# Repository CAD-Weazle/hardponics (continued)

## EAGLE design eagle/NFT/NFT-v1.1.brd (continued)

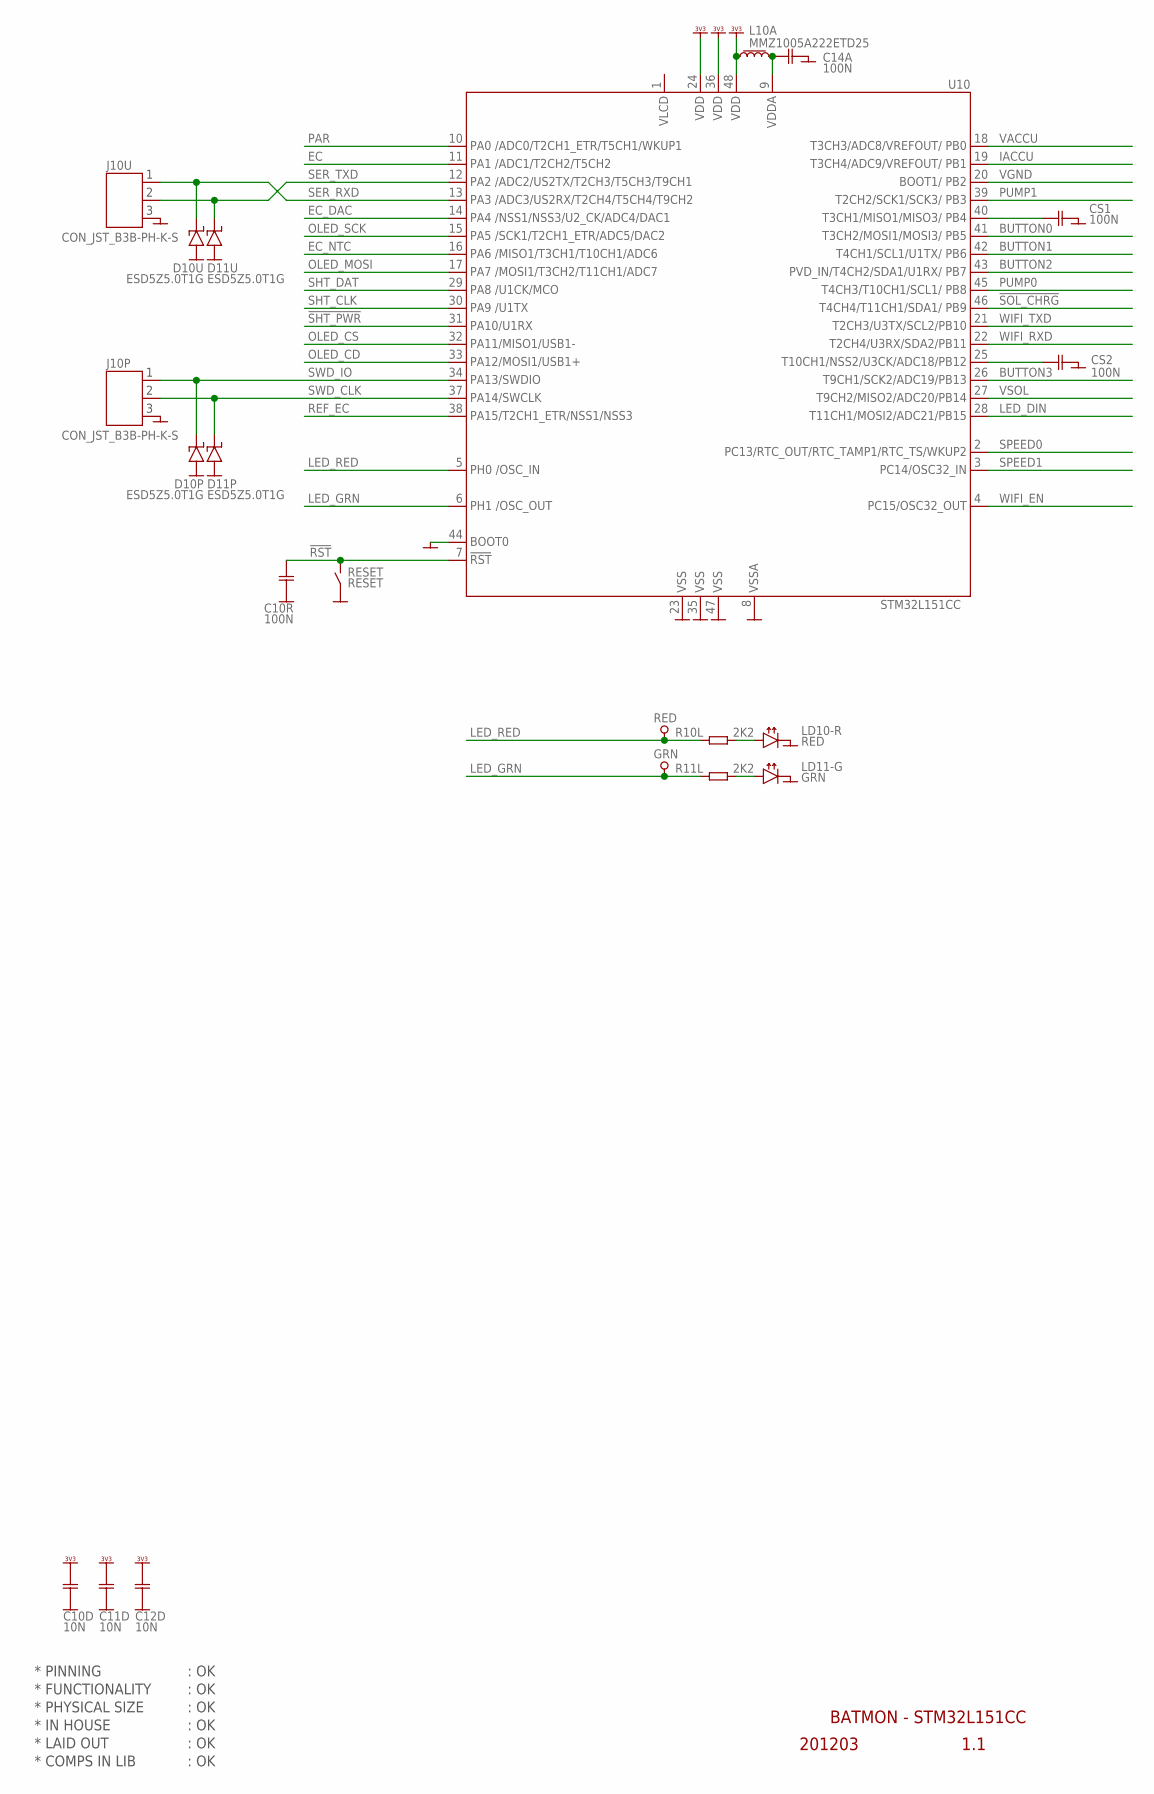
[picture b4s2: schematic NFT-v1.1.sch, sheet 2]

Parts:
C10D, C11D, C12D: 10N; CAP0402
C10R, C14A: 100N; CAP0402
CS1, CS2: 100N; CAP0402
D10P, D10U, D11P, D11U: ESD5Z5.0T1G; DIODE_SOD523
GRN: PIN_TEST_0.6MM; HOLE_PTH_0.6MM
J10P, J10U: CON_JST_B3B-PH-K-S
L10A: MMZ1005A222ETD25; L_0402
LD10-R: RED; LED_SMD_0402
LD11-G: GRN; LED_SMD_0402
R10L, R11L: 2K2; RES0402
RED: PIN_TEST_0.6MM; HOLE_PTH_0.6MM
RESET: RESET; SWITCH_SMD_PBUTTON_2P
U10: STM32L151CC; LQFP48

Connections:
!RST: C10R.1, RESET.1 (1-2), U10.7 (7.!RST)
!SHT_PWR: U10.31 (31.PA10); also elsewhere on the board
!SOL_CHRG: U10.46 (46.PB9); also elsewhere on the board
BUTTON0: U10.41 (41.PB5); also elsewhere on the board
BUTTON1: U10.42 (42.PB6); also elsewhere on the board
BUTTON2: U10.43 (43.PB7); also elsewhere on the board
BUTTON3: U10.26 (26.PB13); also elsewhere on the board
CSAMPLE: CS1.1, U10.40 (40.PB4)
CSAMPLE1: CS2.1, U10.25 (25.PB12)
EC: U10.11 (11.PA1); also elsewhere on the board
EC_DAC: U10.14 (14.PA4); also elsewhere on the board
EC_NTC: U10.16 (16.PA6); also elsewhere on the board
GND: C10D.2, C10R.2, C11D.2, C12D.2, C14A.2, CS1.2, CS2.2, D10P.A, D10U.A, D11P.A, D11U.A, J10P.3, J10U.3, LD10-R.C, LD11-G.C, RESET.2 (3-4), U10.8 (8.GND), U10.23 (23.GND), U10.35 (35.GND), U10.44 (44.BOOT0), U10.47 (47.GND); also elsewhere on the board
IACCU: U10.19 (19.PB1); also elsewhere on the board
LED_DIN: U10.28 (28.PB15); also elsewhere on the board
LED_GRN: GRN.1, R11L.1, U10.6 (6.OSC_OUT)
LED_RED: R10L.1, RED.1, U10.5 (5.OSC_IN)
unnamed: LD11-G.A, R11L.2
unnamed: LD10-R.A, R10L.2
OLED_CD: U10.33 (33.PA12); also elsewhere on the board
OLED_CS: U10.32 (32.PA11); also elsewhere on the board
OLED_MOSI: U10.17 (17.PA7); also elsewhere on the board
OLED_SCK: U10.15 (15.PA5); also elsewhere on the board
PAR: U10.10 (10.PA0); also elsewhere on the board
PUMP0: U10.45 (45.PB8); also elsewhere on the board
PUMP1: U10.39 (39.PB3); also elsewhere on the board
REF_EC: U10.38 (38.PA15); also elsewhere on the board
SER_RXD: D10U.C, J10U.1, U10.13 (13.PA3)
SER_TXD: D11U.C, J10U.2, U10.12 (12.PA2)
SHT_CLK: U10.30 (30.PA9); also elsewhere on the board
SHT_DAT: U10.29 (29.PA8); also elsewhere on the board
SPEED0: U10.2 (2.PC13); also elsewhere on the board
SPEED1: U10.3 (3.PC14); also elsewhere on the board
SWD_CLK: D11P.C, J10P.2, U10.37 (37.PA14)
SWD_IO: D10P.C, J10P.1, U10.34 (34.PA13)
VACCU: U10.18 (18.PB0); also elsewhere on the board
VDDA: C14A.1, L10A.2, U10.9 (9.VDD)
VDD_3V3: C10D.1, C11D.1, C12D.1, L10A.1, U10.24 (24.VDD), U10.36 (36.VDD), U10.48 (48.VDD); also elsewhere on the board
VGND: U10.20 (20.PB2); also elsewhere on the board
VSOL: U10.27 (27.PB14); also elsewhere on the board
WIFI_EN: U10.4 (4.PC15); also elsewhere on the board
WIFI_RXD: U10.22 (22.PB11); also elsewhere on the board
WIFI_TXD: U10.21 (21.PB10); also elsewhere on the board

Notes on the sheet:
* PINNING
* FUNCTIONALITY
* PHYSICAL SIZE
* LAID OUT
* COMPS IN LIB
* IN HOUSE
: OK
BATMON - STM32L151CC
201203
1.1

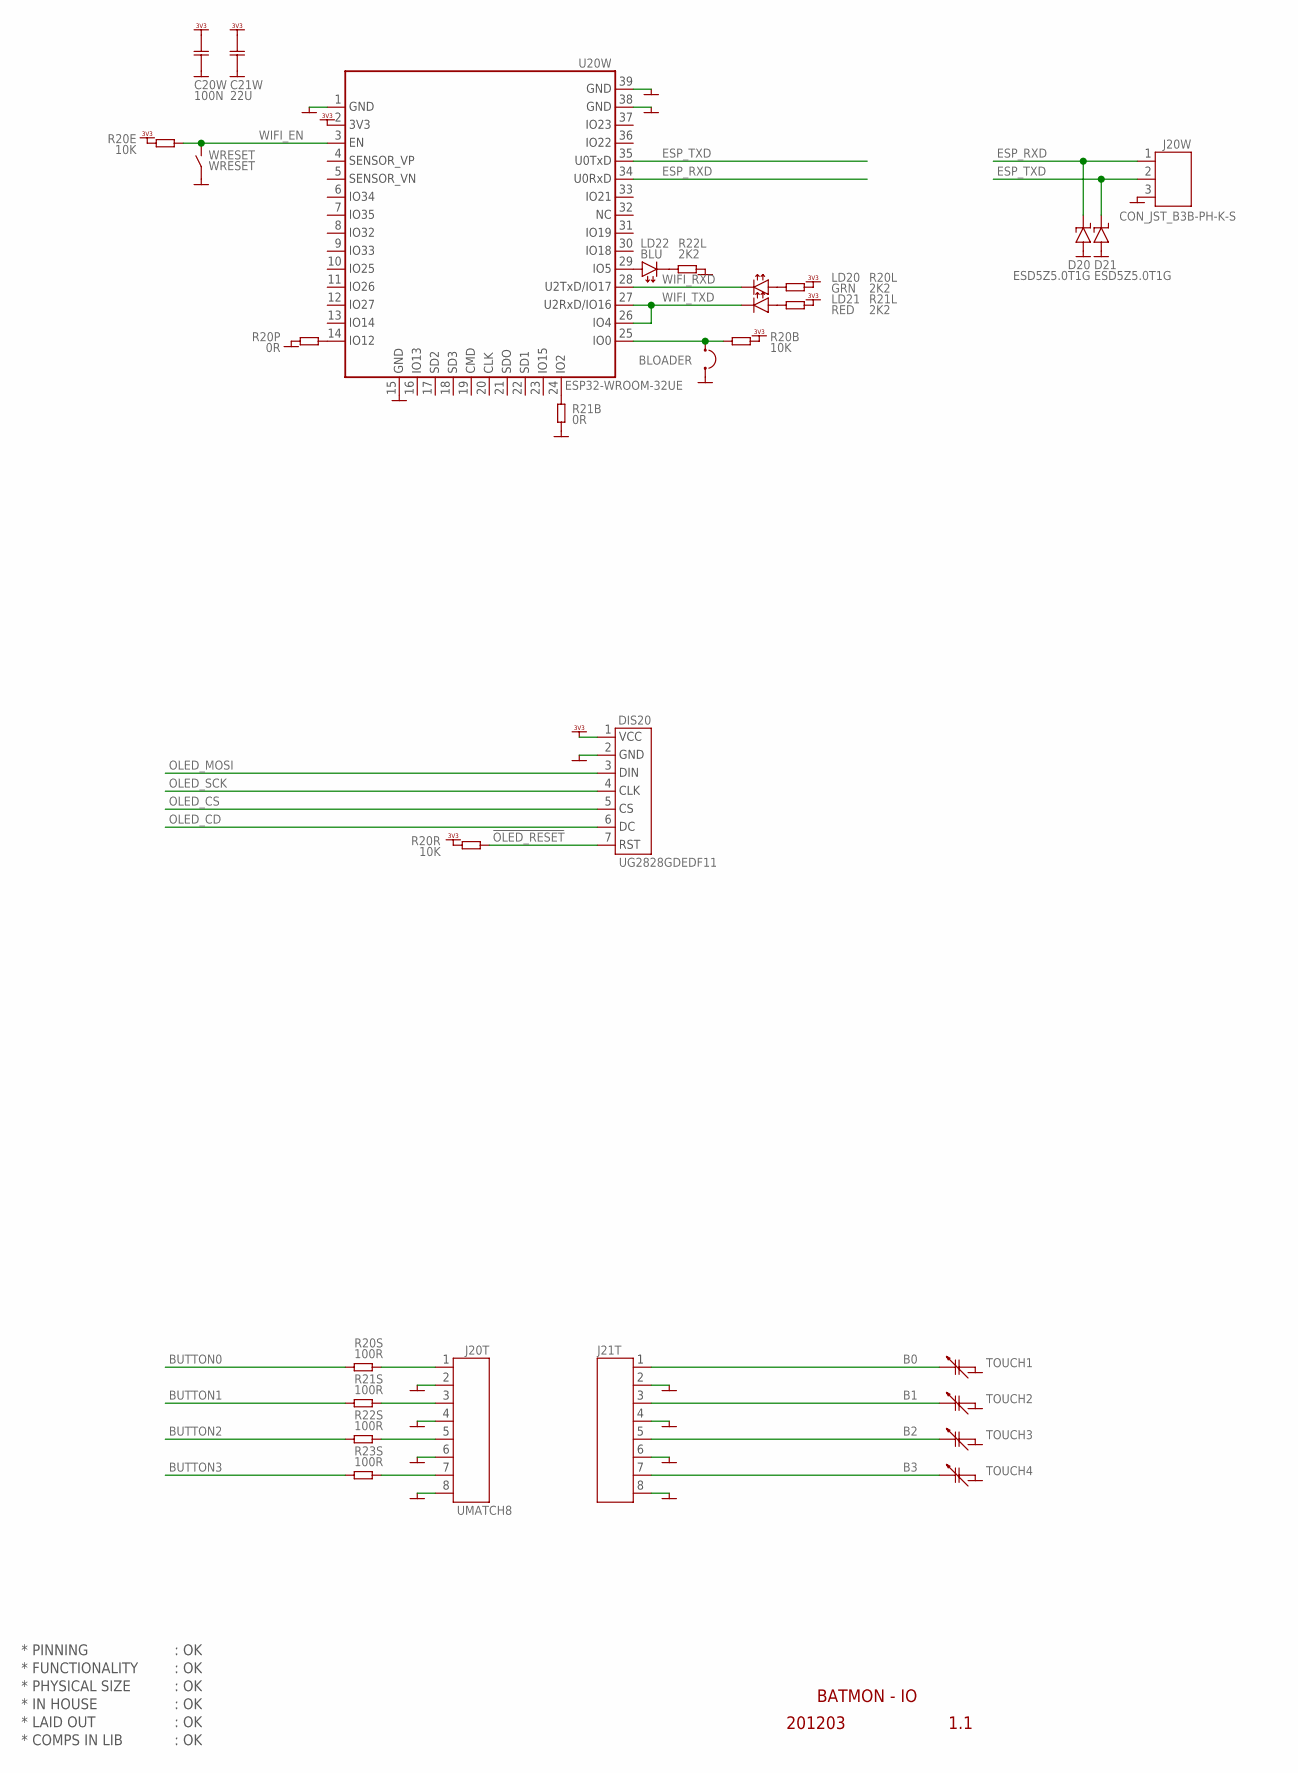
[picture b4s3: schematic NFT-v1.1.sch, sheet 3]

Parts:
BLOADER: GOLD2
C20W: 100N; CAP0402
C21W: 22U; CAP0805
D20, D21: ESD5Z5.0T1G; DIODE_SOD523
DIS20: UG2828GDEDF11; WAVESHARE_1.5"OLED128X128
J20T: UMATCH8; CON_MICROMATCH_TOP_8F
J20W: CON_JST_B3B-PH-K-S
J21T: CON_MICROMATCH_8F_SMD-TOP; CON_MICROMATCH_TOP_8F_SMD
LD20: GRN; LED_SMD_0402
LD21: RED; LED_SMD_0402
LD22: BLU; LED_SMD_0402
R20B, R20E, R20R: 10K; RES0402
R20L, R21L, R22L: 2K2; RES0402
R20P, R21B: 0R; RES0402
R20S, R21S, R22S, R23S: 100R; RES0402
TOUCH1, TOUCH2, TOUCH3, TOUCH4: CAP_TOUCH_ROUND_10MM_SINGLE
U20W: ESP32-WROOM-32UE
WRESET: WRESET; SWITCH_SMD_PBUTTON_2P

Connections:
!OLED_RESET: DIS20.7 (7.RST), R20R.2
B0: J20T.1, J21T.1, R20S.2, TOUCH1.1
B1: J20T.3, J21T.3, R21S.2, TOUCH2.1
B2: J20T.5, J21T.5, R22S.2, TOUCH3.1
B3: J20T.7, J21T.7, R23S.2, TOUCH4.1
BUTTON0: R20S.1; also elsewhere on the board
BUTTON1: R21S.1; also elsewhere on the board
BUTTON2: R22S.1; also elsewhere on the board
BUTTON3: R23S.1; also elsewhere on the board
ESP_RXD: D20.C, J20W.1, U20W.34 (34.RXD0)
ESP_TXD: D21.C, J20W.2, U20W.35 (35.TXD0)
GND: BLOADER.2, C20W.2, C21W.2, D20.A, D21.A, DIS20.2 (2.GND), J20T.2, J20T.4, J20T.6, J20T.8, J20W.3, J21T.2, J21T.4, J21T.6, J21T.8, R20P.2, R21B.2, R22L.1, TOUCH1.2, TOUCH2.2, TOUCH3.2, TOUCH4.2, U20W.1 (1.GND), U20W.15 (15.GND), U20W.38 (38.GND), U20W.GND (39.GND), WRESET.2 (3-4); also elsewhere on the board
unnamed: BLOADER.1, R20B.1, U20W.25 (25.IO0)
unnamed: LD20.A, R20L.2
unnamed: LD21.A, R21L.2
unnamed: R21B.1, U20W.24 (24.IO2)
unnamed: R20P.1, U20W.14 (14.IO12)
unnamed: LD22.C, R22L.2
OLED_CD: DIS20.6 (6.DC); also elsewhere on the board
OLED_CS: DIS20.5 (5.CS); also elsewhere on the board
OLED_MOSI: DIS20.3 (3.DIN); also elsewhere on the board
OLED_SCK: DIS20.4 (4.CLK); also elsewhere on the board
VDD_3V3: C20W.1, C21W.1, DIS20.1 (1.VCC), R20B.2, R20E.2, R20L.1, R20R.1, R21L.1, U20W.2 (2.3V3); also elsewhere on the board
WIFI_EN: R20E.1, U20W.3 (3.EN), WRESET.1 (1-2); also elsewhere on the board
WIFI_LED: LD22.A, U20W.29 (29.IO5)
WIFI_RXD: LD20.C, U20W.28 (28.IO17); also elsewhere on the board
WIFI_TXD: LD21.C, U20W.26 (26.IO4), U20W.27 (27.IO16); also elsewhere on the board

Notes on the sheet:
* PINNING
* FUNCTIONALITY
* PHYSICAL SIZE
* LAID OUT
* COMPS IN LIB
* IN HOUSE
BATMON - IO
201203
1.1
: OK

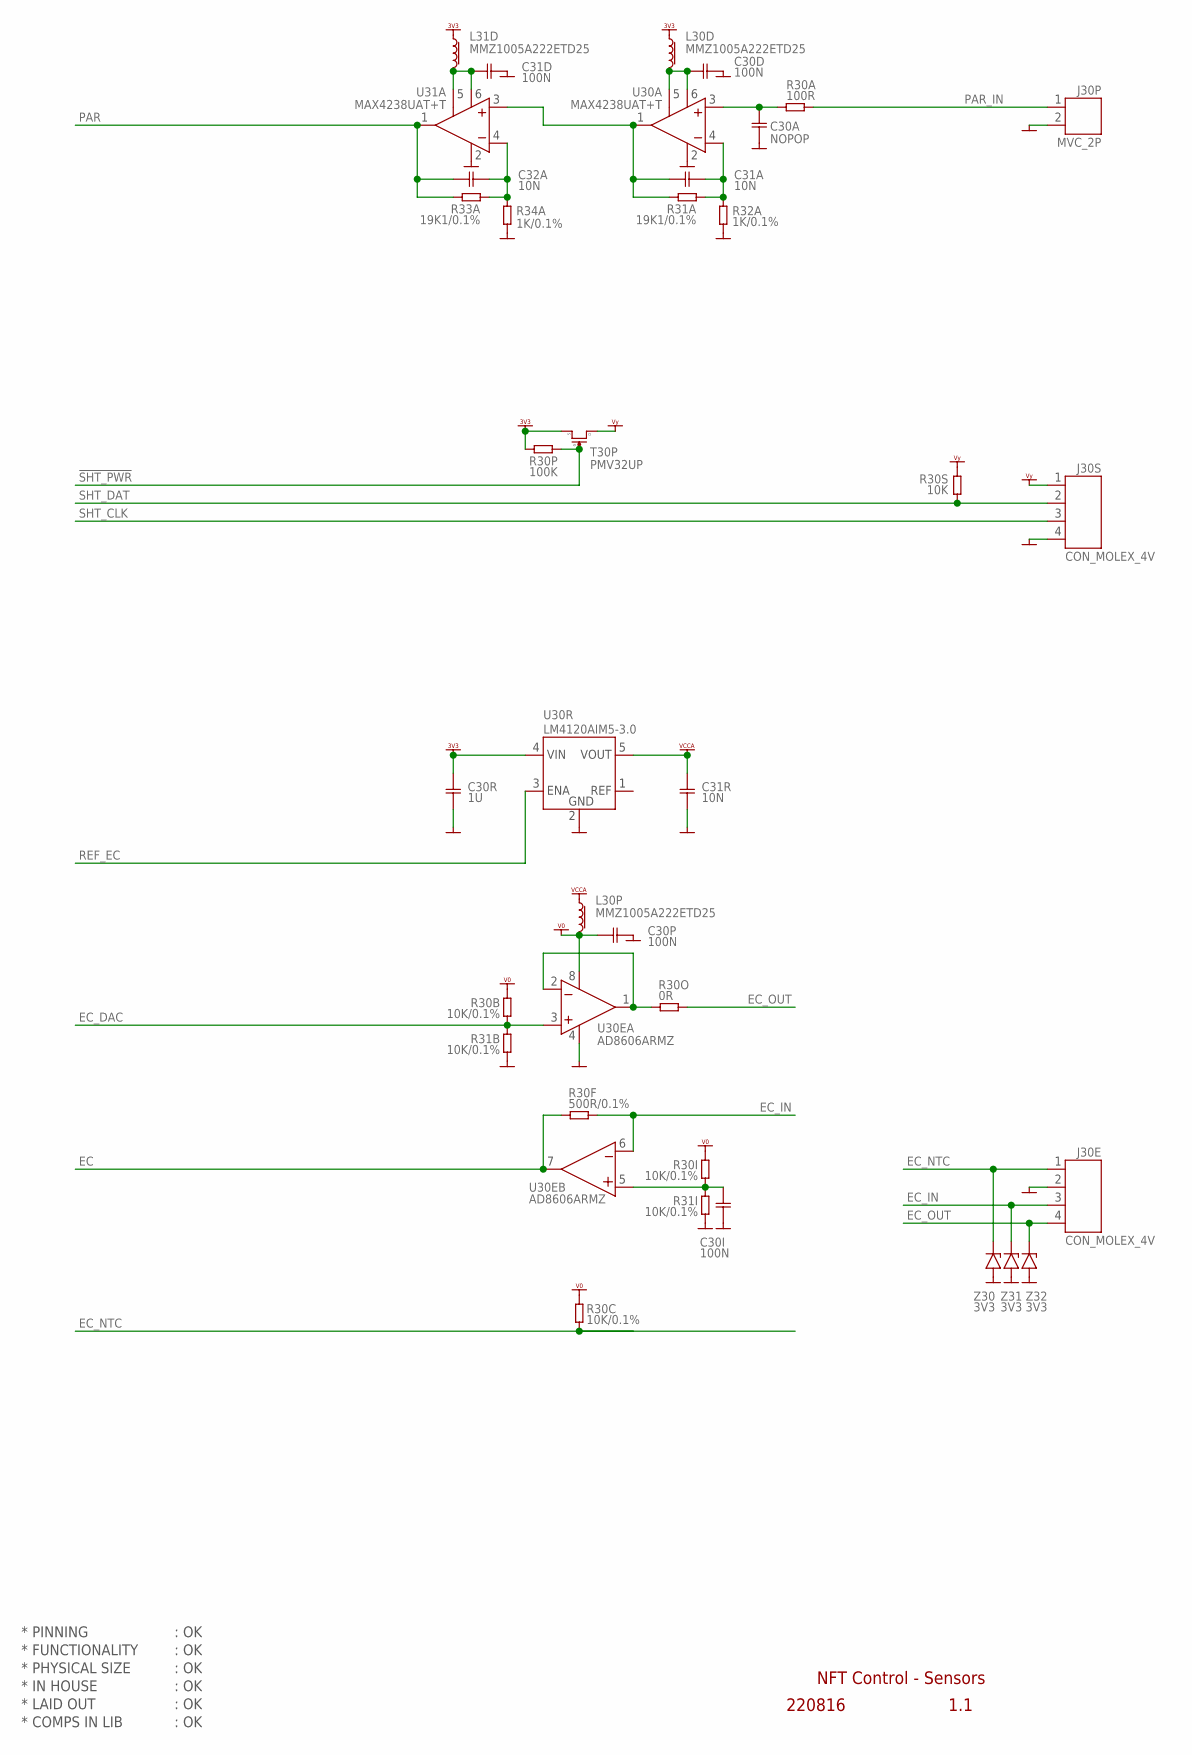
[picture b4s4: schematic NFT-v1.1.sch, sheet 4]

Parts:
C30A: NOPOP; CAP0402
C30D, C30I, C30P, C31D: 100N; CAP0402
C30R: 1U; CAP0402
C31A, C31R, C32A: 10N; CAP0402
J30E, J30S: CON_MOLEX_4V
J30P: MVC_2P; CON_PHOENIX_COMBICON_MCV_HEADER_P
L30D, L30P, L31D: MMZ1005A222ETD25; L_0402
R30A: 100R; RES0402
R30B, R30C, R30I, R31B, R31I: 10K/0.1%; RES0402
R30F: 500R/0.1%; RES0603
R30O: 0R; RES0402
R30P: 100K; RES0402
R30S: 10K; RES0402
R31A, R33A: 19K1/0.1%; RES0402
R32A, R34A: 1K/0.1%; RES0402
T30P: PMV32UP; PFET_SOT23
U30A, U31A: MAX4238UAT+T; SOT23-6
U30E: AD8606ARMZ; MSOP8
U30R: LM4120AIM5-3.0; SOT23-5
Z30, Z31, Z32: 3V3; ZENER_SOD80

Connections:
!SHT_PWR: R30P.2, T30P.1 (G); also elsewhere on the board
EC: R30F.2, U30E.7 (7.OUT); also elsewhere on the board
EC30_BUF: R30O.2, U30E.1 (1.OUT), U30E.2 (2.IN-)
EC_DAC: R30B.2, R31B.1, U30E.3 (3.IN+); also elsewhere on the board
EC_IN: J30E.3, R30F.1, U30E.6 (6.IN-), Z31.2 (C)
EC_NTC: J30E.1, R30C.2, Z30.2 (C); also elsewhere on the board
EC_OUT: J30E.4, R30O.1, Z32.2 (C)
GND: C30A.1, C30D.2, C30I.1, C30P.2, C30R.2, C31D.2, C31R.2, J30E.2, J30P.2, J30S.4, R31B.2, R31I.2, R32A.2, R34A.2, U30A.2 (2.V-), U30E.4 (4.V-), U30R.2 (2.GND), U31A.2 (2.V-), Z30.1 (A), Z31.1 (A), Z32.1 (A); also elsewhere on the board
IMUXF: C30A.2, R30A.2, U30A.3 (3.IN+)
unnamed: C31D.1, L31D.2, U31A.5 (5.!SHDN), U31A.6 (6.V+)
unnamed: C30I.2, R30I.2, R31I.1, U30E.5 (5.IN+)
unnamed: C30D.1, L30D.2, U30A.5 (5.!SHDN), U30A.6 (6.V+)
unnamed: C32A.2, R33A.1, R34A.1, U31A.4 (4.IN-)
unnamed: C31A.1, R31A.2, U30A.1 (1.OUT), U31A.3 (3.IN+)
unnamed: C31A.2, R31A.1, R32A.1, U30A.4 (4.IN-)
PAR: C32A.1, R33A.2, U31A.1 (1.OUT); also elsewhere on the board
PAR_IN: J30P.1, R30A.1
REF_EC: U30R.3 (3.ENA); also elsewhere on the board
SHT_CLK: J30S.3; also elsewhere on the board
SHT_DAT: J30S.2, R30S.2; also elsewhere on the board
V0: C30P.1, L30P.2, R30B.1, R30C.1, R30I.1, U30E.8 (8.V+)
VCCA: C31R.1, L30P.1, U30R.5 (5.VOUT)
VDD_3V3: C30R.1, L30D.1, L31D.1, R30P.1, T30P.2 (S), U30R.4 (4.VIN); also elsewhere on the board
VY: J30S.1, R30S.1, T30P.3 (D)

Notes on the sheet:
* PINNING
* FUNCTIONALITY
* PHYSICAL SIZE
* LAID OUT
* COMPS IN LIB
* IN HOUSE
NFT Control - Sensors
220816
1.1
: OK

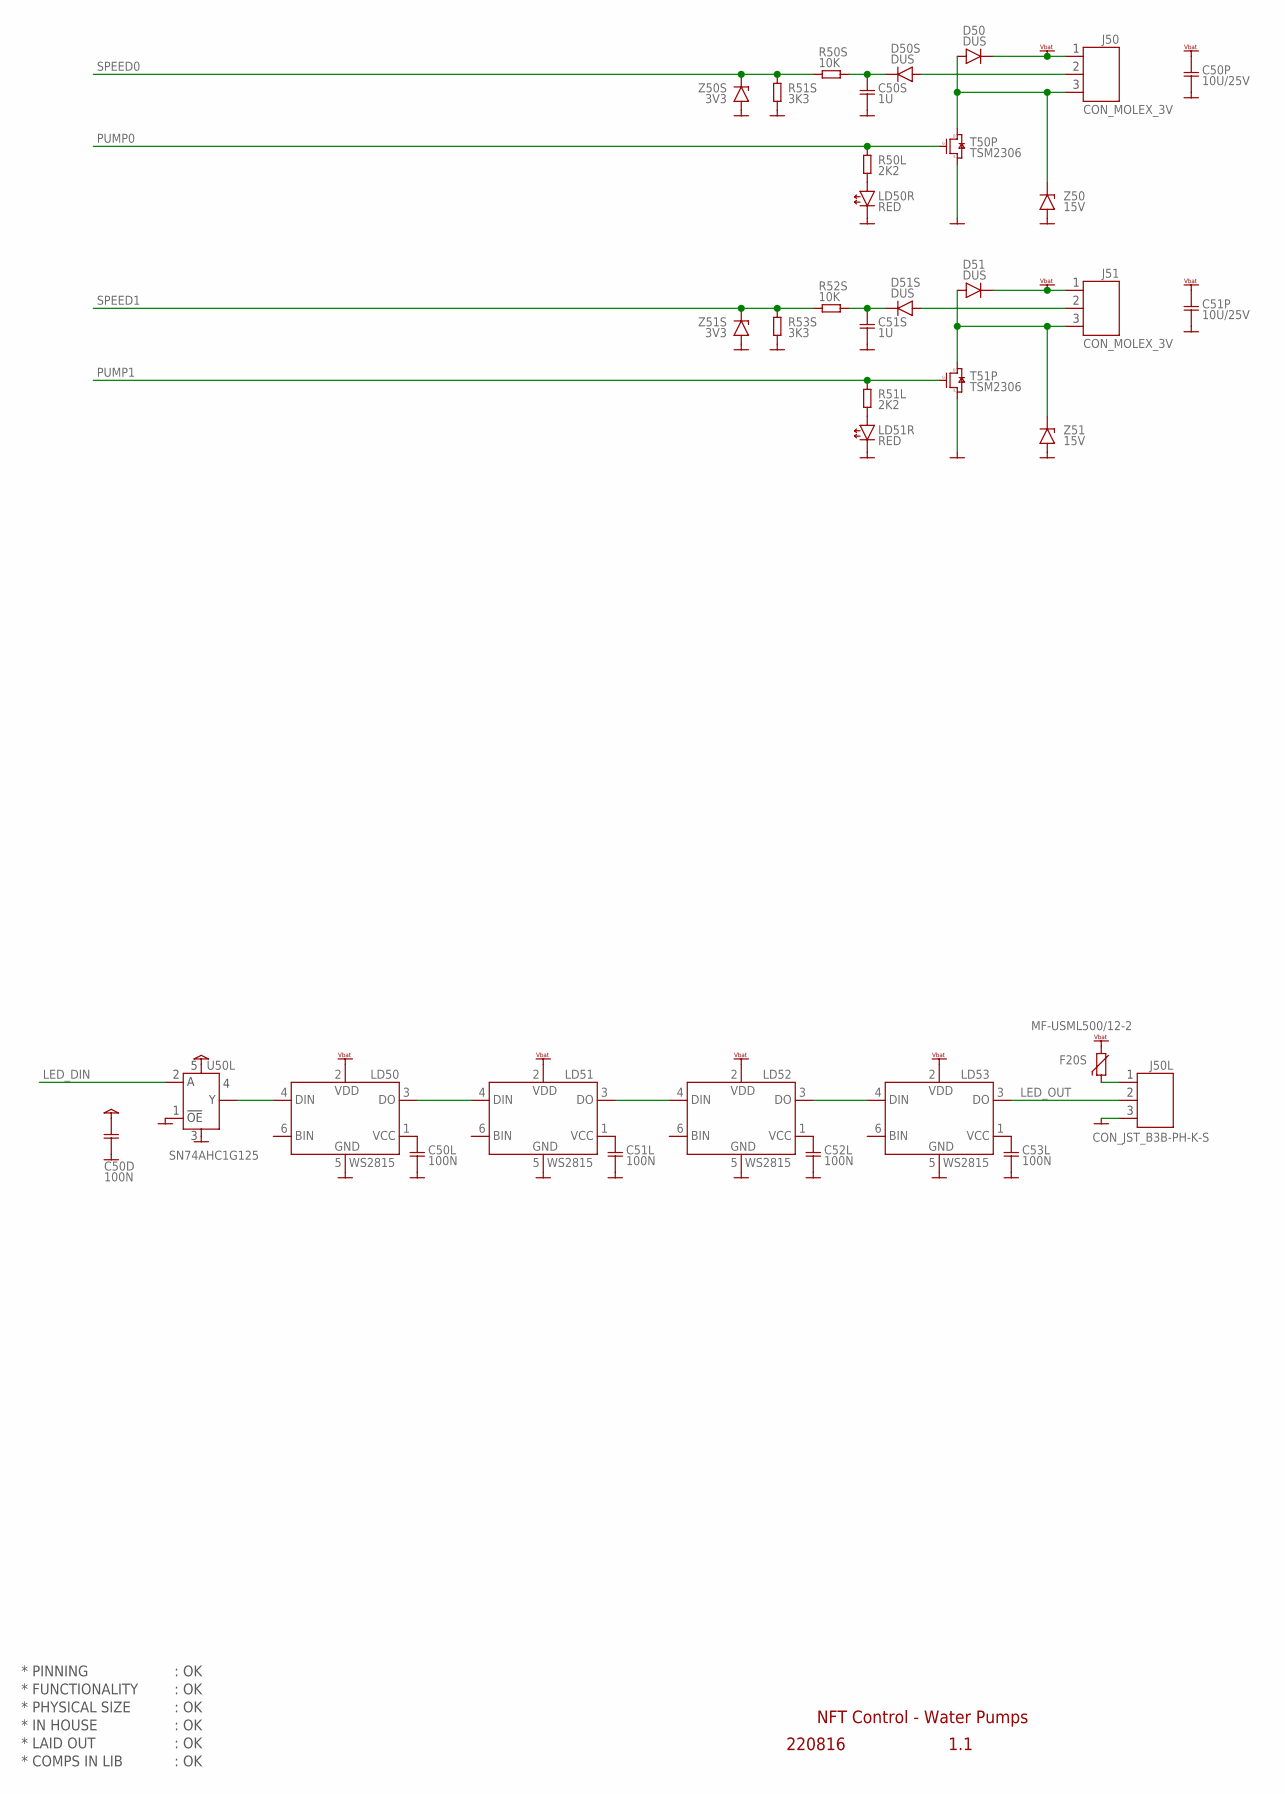
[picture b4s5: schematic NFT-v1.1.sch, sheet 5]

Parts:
C50D, C50L, C51L, C52L, C53L: 100N; CAP0402
C50P, C51P: 10U/25V; CAP1210
C50S, C51S: 1U; CAP0402
D50, D50S, D51, D51S: DUS; DIODE_SOD323
F20S: MF-USML500/12-2; RES1210
J50, J51: CON_MOLEX_3V
J50L: CON_JST_B3B-PH-K-S
LD50, LD51, LD52, LD53: WS2815
LD50R, LD51R: RED; LED_SMD_0402
R50L, R51L: 2K2; RES0402
R50S, R52S: 10K; RES0402
R51S, R53S: 3K3; RES0402
T50P, T51P: TSM2306; NFET_SOT23
U50L: SN74AHC1G125; SOT553-5
Z50, Z51: 15V; ZENER_SOD80
Z50S, Z51S: 3V3; ZENER_SOD80

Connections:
DI: LD50.4 (4.DIN), U50L.4 (4.Y)
GND: C50D.2, C50L.2, C50P.2, C50S.2, C51L.2, C51P.2, C51S.2, C52L.2, C53L.2, J50L.3, LD50.5 (5.GND), LD50R.C, LD51.5 (5.GND), LD51R.C, LD52.5 (5.GND), LD53.5 (5.GND), R51S.2, R53S.2, T50P.S (S2), T51P.S (S2), U50L.1 (1.OE), U50L.3 (3.GND), Z50.1 (A), Z50S.1 (A), Z51.1 (A), Z51S.1 (A); also elsewhere on the board
LED_DIN: U50L.2 (2.A); also elsewhere on the board
LED_OUT: J50L.2, LD53.3 (3.DO)
unnamed: C50L.1, LD50.1 (1.VCC)
unnamed: C51L.1, LD51.1 (1.VCC)
unnamed: C52L.1, LD52.1 (1.VCC)
unnamed: C53L.1, LD53.1 (1.VCC)
unnamed: LD51R.A, R51L.2
unnamed: C50S.1, D50S.C (-), R50S.2
unnamed: C51S.1, D51S.C (-), R52S.2
unnamed: F20S.1, J50L.1
unnamed: LD50R.A, R50L.2
P0: D50.A (+), J50.3, T50P.D (D3), Z50.2 (C)
P1: D51.A (+), J51.3, T51P.D (D3), Z51.2 (C)
PUMP0: R50L.1, T50P.G (G1); also elsewhere on the board
PUMP1: R51L.1, T51P.G (G1); also elsewhere on the board
S0: D50S.A (+), J50.2
S1: D51S.A (+), J51.2
SPEED0: R50S.1, R51S.1, Z50S.2 (C); also elsewhere on the board
SPEED1: R52S.1, R53S.1, Z51S.2 (C); also elsewhere on the board
VBAT: C50P.1, C51P.1, D50.C (-), D51.C (-), F20S.2, J50.1, J51.1, LD50.2 (2.VDD), LD51.2 (2.VDD), LD52.2 (2.VDD), LD53.2 (2.VDD); also elsewhere on the board
VCC: C50D.1, U50L.5 (5.VDD); also elsewhere on the board
X0: LD50.3 (3.DO), LD51.4 (4.DIN)
X1: LD51.3 (3.DO), LD52.4 (4.DIN)
X2: LD52.3 (3.DO), LD53.4 (4.DIN)

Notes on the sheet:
* PINNING
* FUNCTIONALITY
* PHYSICAL SIZE
* LAID OUT
* COMPS IN LIB
* IN HOUSE
NFT Control - Water Pumps
220816
1.1
: OK

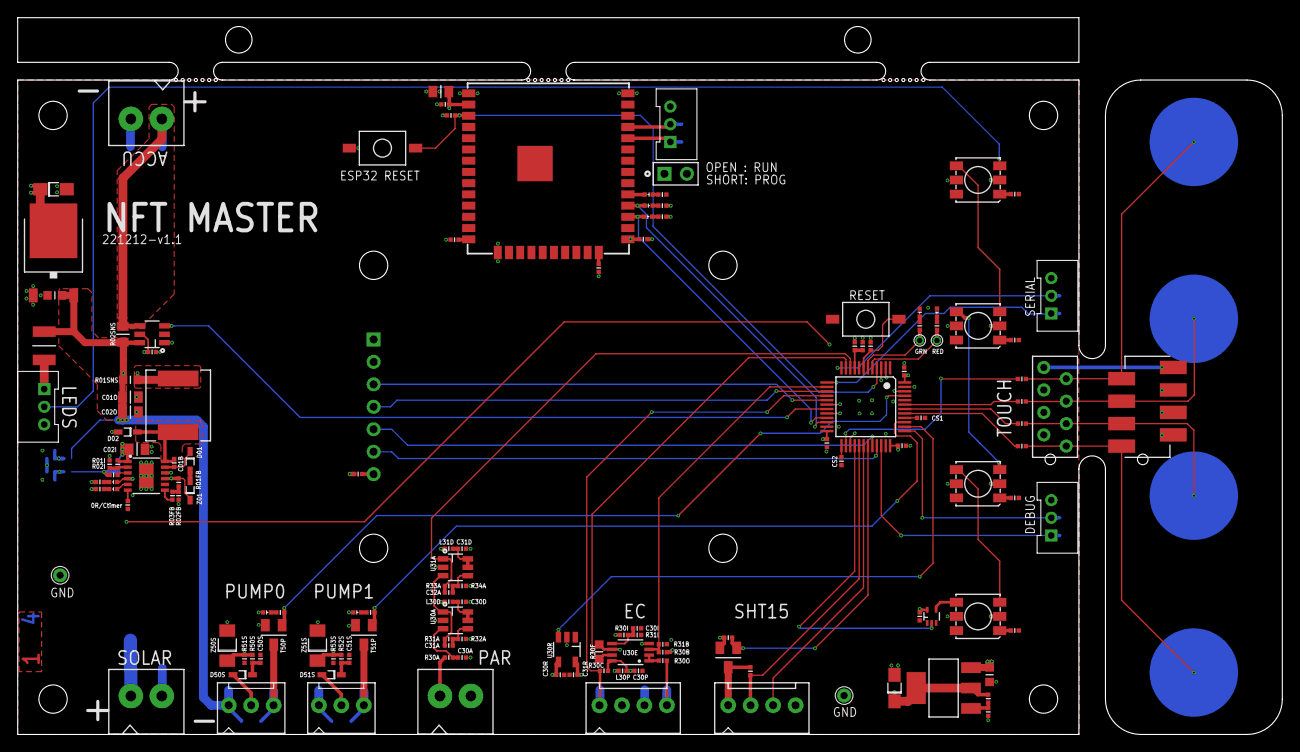
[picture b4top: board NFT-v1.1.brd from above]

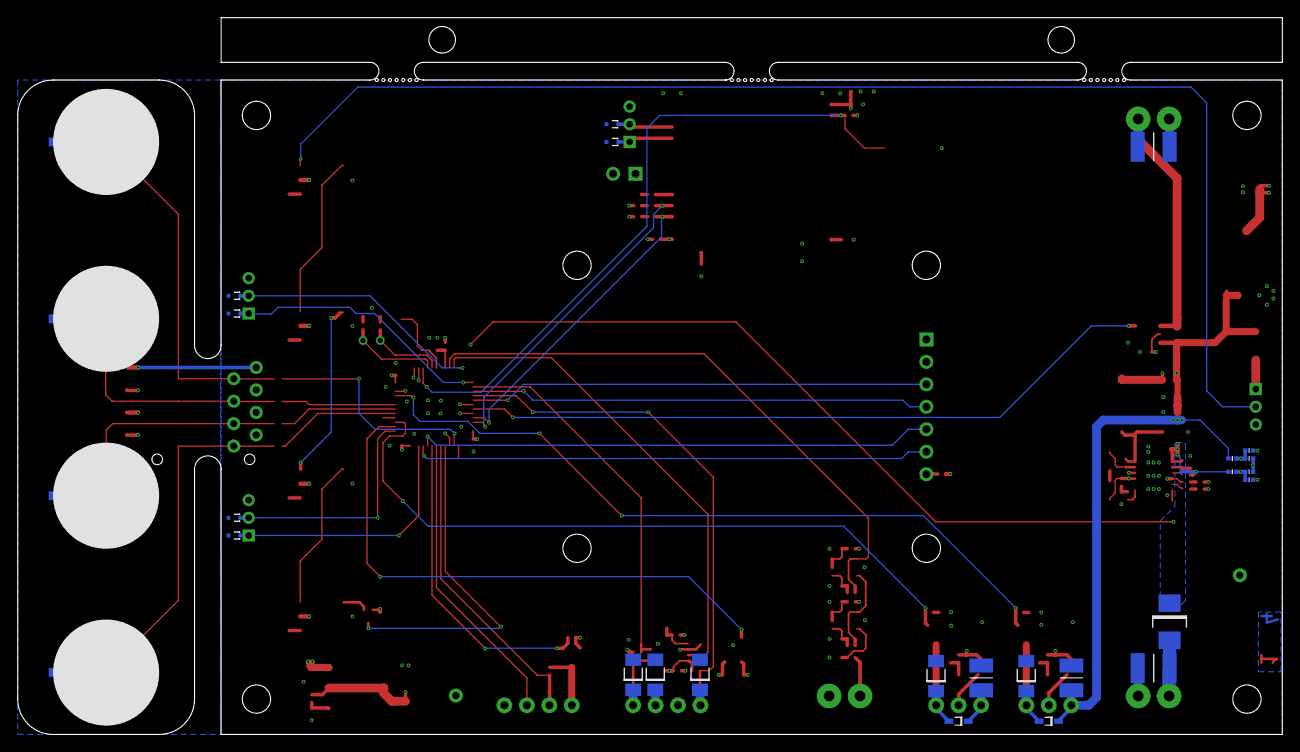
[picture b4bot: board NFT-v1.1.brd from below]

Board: 4 copper layers, 143.0 x 81.0 mm, 179 parts (28 on the bottom side), 107 nets.

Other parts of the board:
U$132, U$133, U$134: EC_MOUSEBITES
U$136, U$137: EC_TOOL-REGISTRATION

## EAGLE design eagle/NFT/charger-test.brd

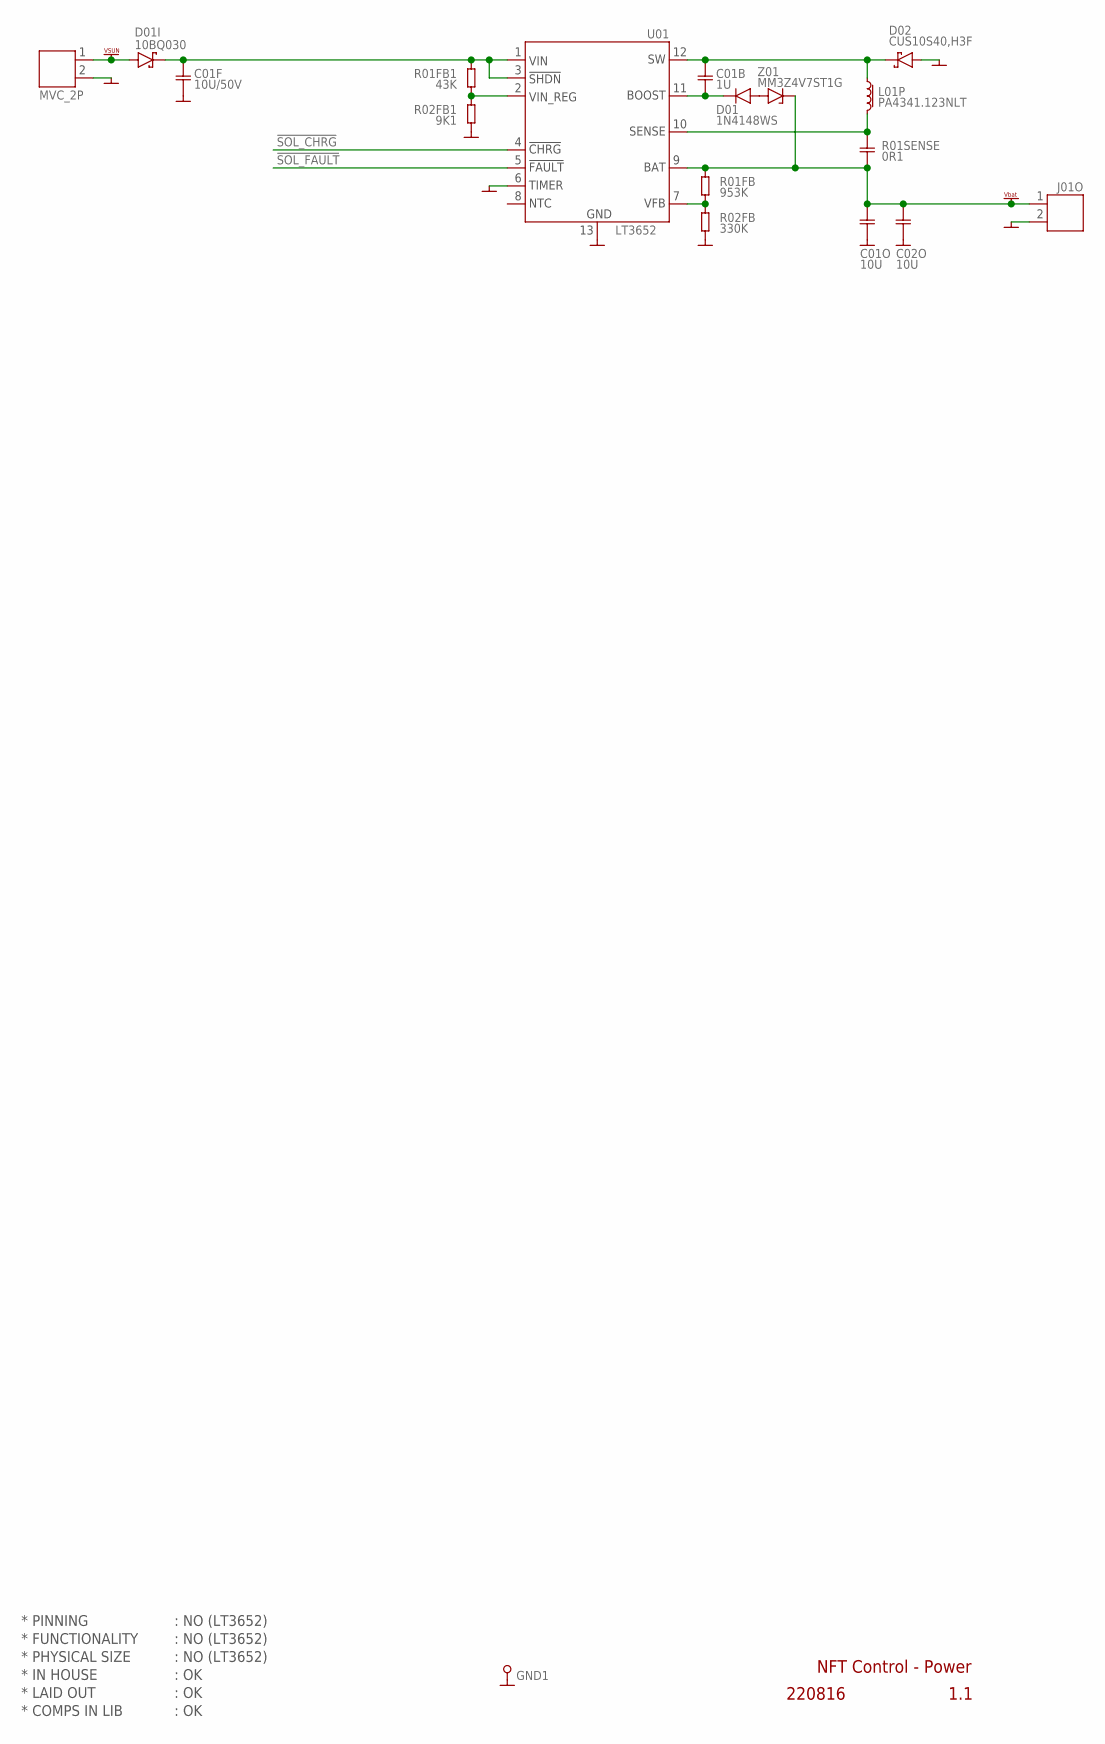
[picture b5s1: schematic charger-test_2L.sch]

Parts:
C01B: 1U; CAP0402
C01F: 10U/50V; CAP0805
C01O, C02O: 10U; CAP0805
D01: 1N4148WS; DIODE_SOD323
D01I: 10BQ030; DIODE_SMB
D02: CUS10S40,H3F; DIODE_SOD323
GND1: PIN_TEST; HOLE_PTH_0.8MM
J01I: MVC_2P; CON_PHOENIX_COMBICON_MCV_HEADER_P
J01O: CON_PHOENIX_COMBICON_MCV_HEADER_2P; CON_PHOENIX_COMBICON_MCV_HEADER_P
L01P: PA4341.123NLT; L_PA4341
R01FB: 953K; RES0402
R01FB1: 43K; RES0603
R01SENSE: 0R1; CAP0603
R02FB: 330K; RES0402
R02FB1: 9K1; RES0603
U01: LT3652; MSOP-12_GND
Z01: MM3Z4V7ST1G; ZENER_SOD323

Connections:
!SOL_CHRG: U01.4 (4.!CHRG)
!SOL_FAULT: U01.5 (5.!FAULT)
BOOST: C01B.2, D01.C (-), U01.11 (11.BOOST)
GND: C01F.2, C01O.2, C02O.2, D02.A, GND1.1, J01I.2, J01O.2, R02FB.1, R02FB1.1, U01.6 (6.TIMER), U01.13 (GND_PAD)
unnamed: C01F.1, D01I.C (-), R01FB1.2, U01.1 (1.VIN), U01.3 (3.!SHDN)
unnamed: D01.A (+), Z01.A
unnamed: R01FB1.1, R02FB1.2, U01.2 (2.VIN_REG)
SENSE: L01P.P$2 (2), R01SENSE.2, U01.10 (10.SENSE)
SW: C01B.1, D02.C, L01P.P$1 (1), U01.12 (12.SW)
VBAT: C01O.1, C02O.1, J01O.1, R01FB.2, R01SENSE.1, U01.9 (9.BAT), Z01.C
VFB: R01FB.1, R02FB.2, U01.7 (7.VFB)
VSUN: D01I.A (+), J01I.1

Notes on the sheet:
* PINNING
* FUNCTIONALITY
* PHYSICAL SIZE
* LAID OUT
* COMPS IN LIB
* IN HOUSE
NFT Control - Power
220816
1.1
: NO (LT3652)
: OK

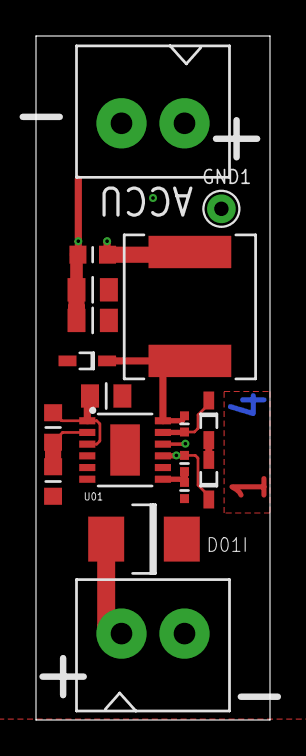
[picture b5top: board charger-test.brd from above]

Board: 4 copper layers, 13.0 x 38.0 mm, 18 parts (0 on the bottom side), 10 nets.
